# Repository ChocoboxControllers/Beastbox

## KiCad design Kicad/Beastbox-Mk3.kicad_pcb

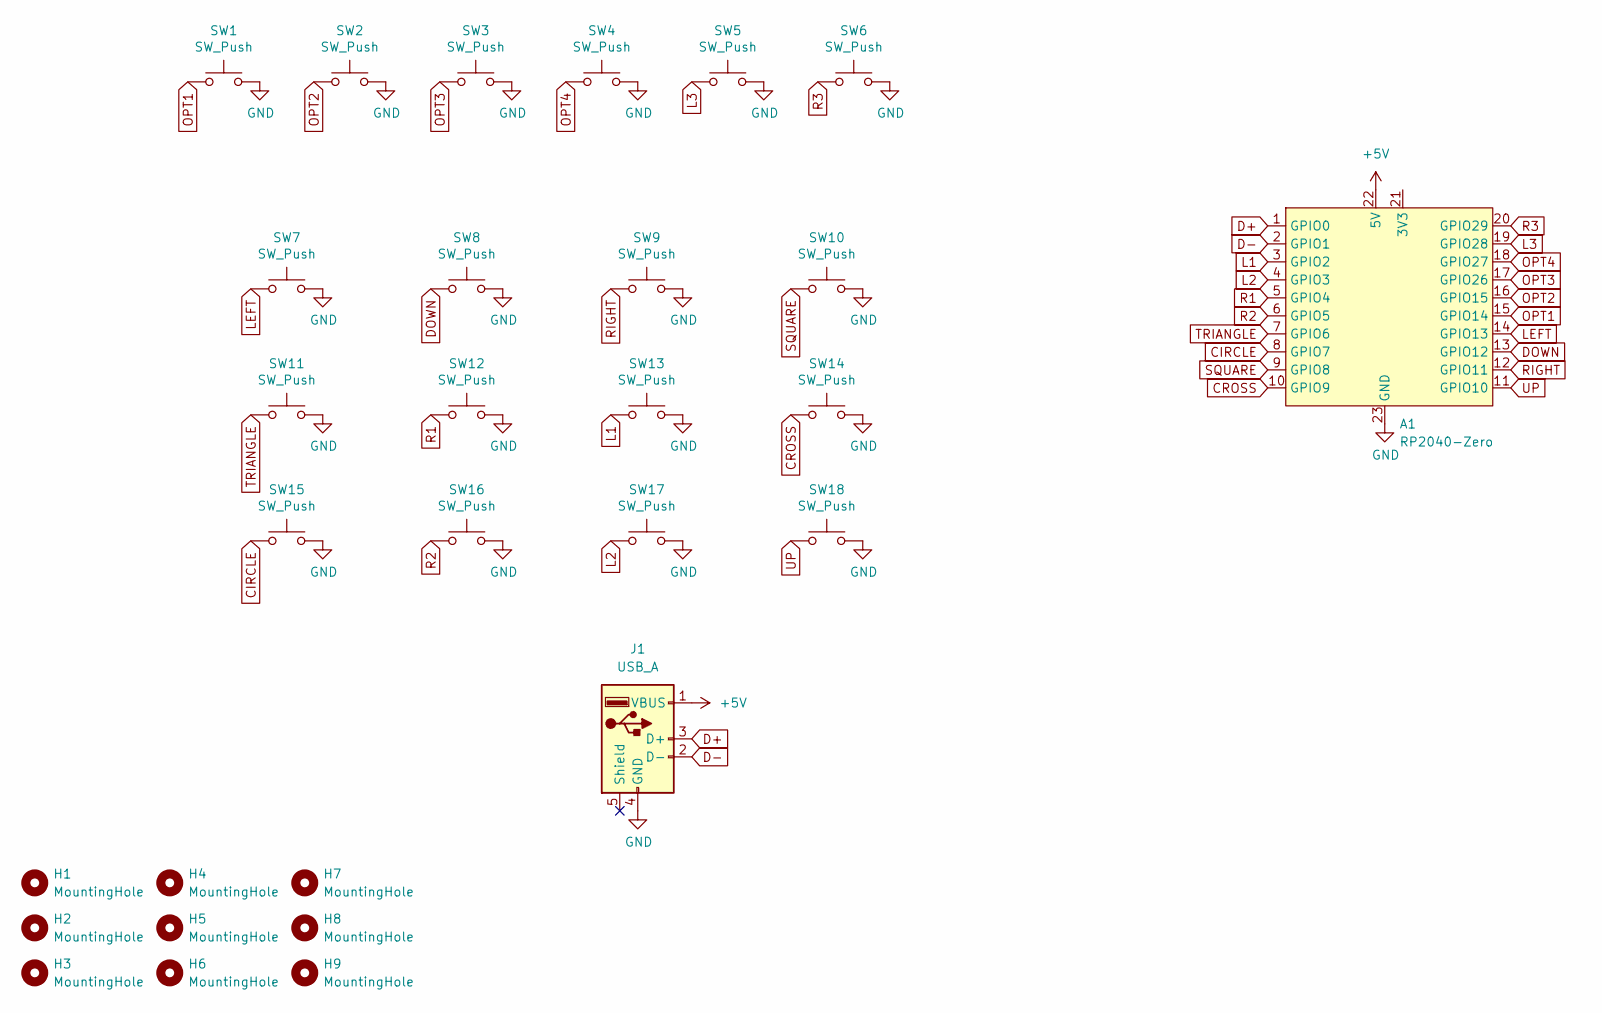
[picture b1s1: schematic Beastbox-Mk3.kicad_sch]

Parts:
A1: RP2040-Zero
H1, H2, H3, H4, H5, H6, H7, H8, H9: MountingHole; MountingHole_6.4mm_M6
J1: USB_A; USB Pads
SW1, SW2, SW3, SW4: SW_Push; SW_PUSH_6mm_H5mm
SW5, SW6, SW7, SW8, SW9, SW10, SW11, SW12, SW13, SW14, SW15, SW16, SW17, SW18: SW_Push; Kailh_socket_PG1350_optional

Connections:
+5V: A1.22 (5V), J1.1 (VBUS)
CIRCLE: A1.8 (GPIO7), SW15.1
CROSS: A1.10 (GPIO9), SW14.1
D+: A1.1 (GPIO0), J1.3 (D+)
D-: A1.2 (GPIO1), J1.2 (D-)
DOWN: A1.13 (GPIO12), SW8.1
GND: A1.23 (GND), J1.4 (GND), SW1.2, SW2.2, SW3.2, SW4.2, SW5.2, SW6.2, SW7.2, SW8.2, SW9.2, SW10.2, SW11.2, SW12.2, SW13.2, SW14.2, SW15.2, SW16.2, SW17.2, SW18.2
L1: A1.3 (GPIO2), SW13.1
L2: A1.4 (GPIO3), SW17.1
L3: A1.19 (GPIO28), SW5.1
LEFT: A1.14 (GPIO13), SW7.1
OPT1: A1.15 (GPIO14), SW1.1
OPT2: A1.16 (GPIO15), SW2.1
OPT3: A1.17 (GPIO26), SW3.1
OPT4: A1.18 (GPIO27), SW4.1
R1: A1.5 (GPIO4), SW12.1
R2: A1.6 (GPIO5), SW16.1
R3: A1.20 (GPIO29), SW6.1
RIGHT: A1.12 (GPIO11), SW9.1
SQUARE: A1.9 (GPIO8), SW10.1
TRIANGLE: A1.7 (GPIO6), SW11.1
UP: A1.11 (GPIO10), SW18.1

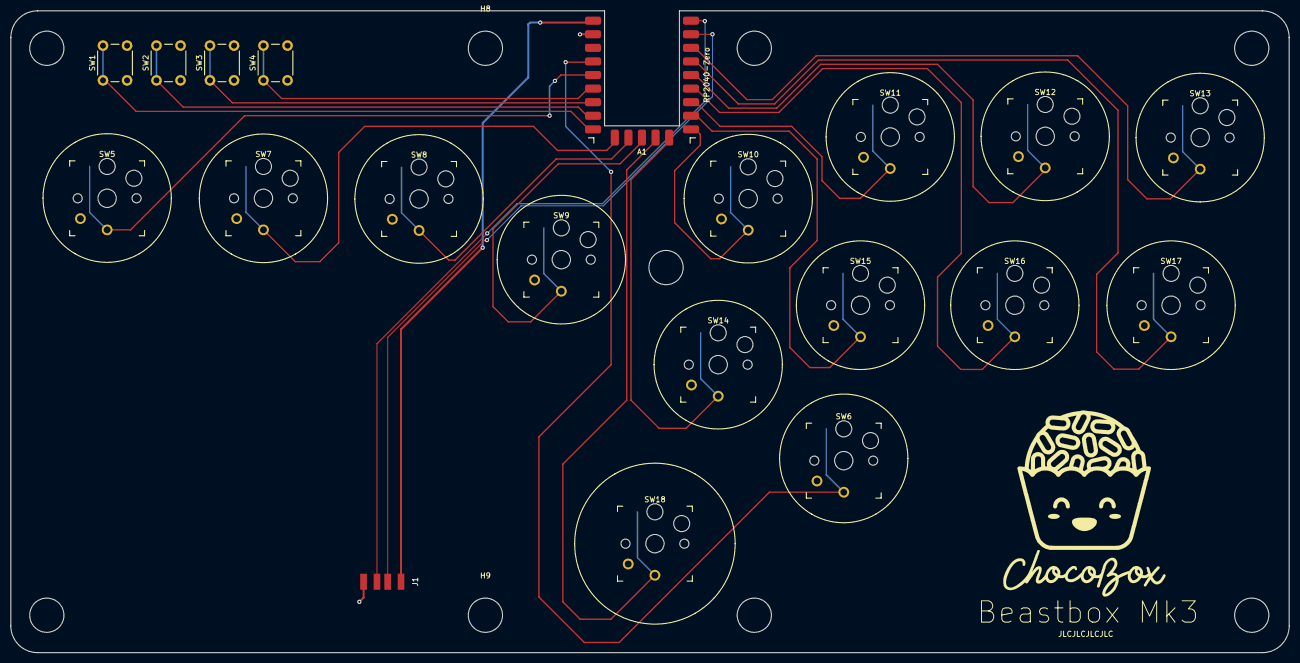
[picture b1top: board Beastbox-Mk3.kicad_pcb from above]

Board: 2 copper layers, 239.0 x 120.0 mm, 30 parts (0 on the bottom side), 22 nets.

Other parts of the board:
Ref**: Val**; silk

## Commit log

2023-12-18 Added bottom 3d file
